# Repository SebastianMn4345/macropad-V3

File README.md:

# macropad-V3
 8-key with oled/slide pot -> no matrix

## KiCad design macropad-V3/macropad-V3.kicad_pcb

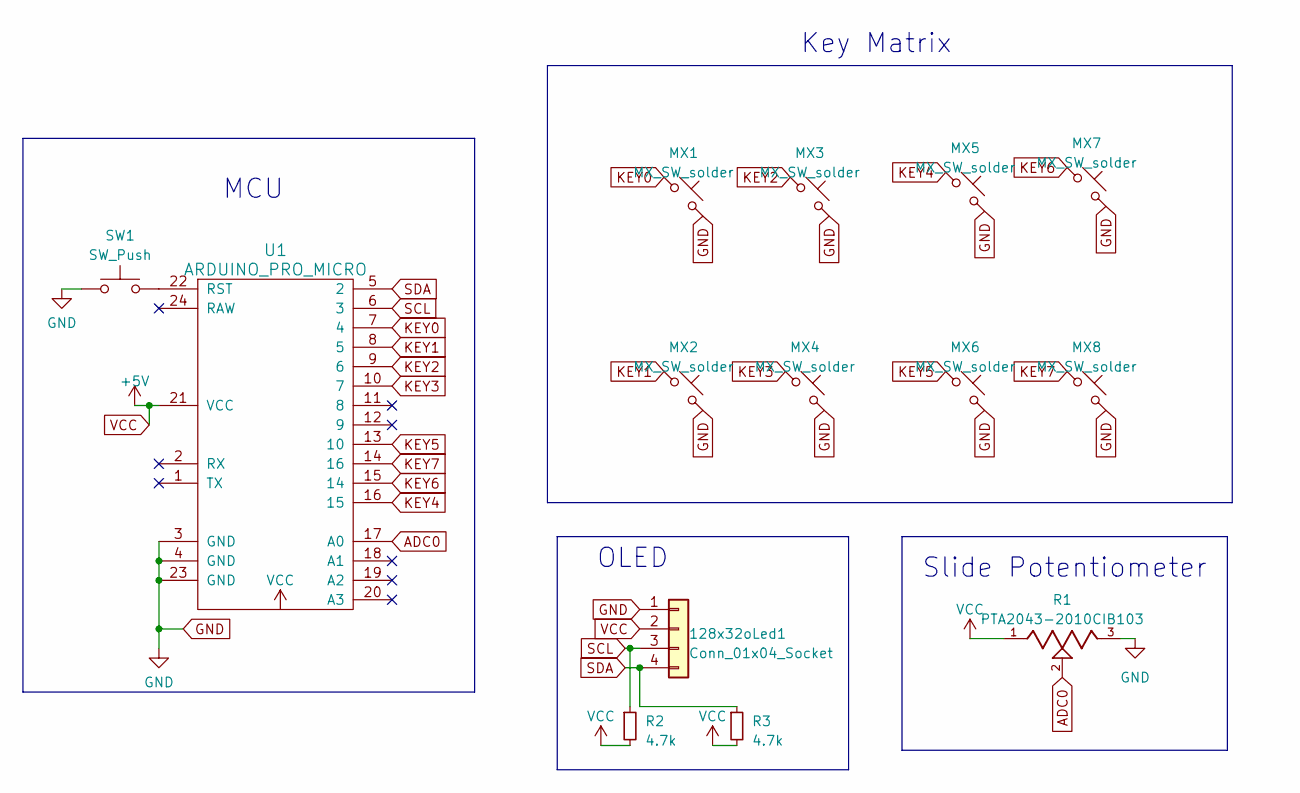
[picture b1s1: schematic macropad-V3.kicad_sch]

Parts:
128x32oLed1: Conn_01x04_Socket; SSD1306-0.91-OLED-4pin-128x32
MX1, MX2, MX3, MX4, MX5, MX6, MX7, MX8: MX_SW_solder; SW_Cherry_MX_1.00u_PCB
R1: PTA2043-2010CIB103; TRIM_PTA2043-2010CIB103; PARTREV 04/21
R2, R3: 4.7k; R_Axial_DIN0309_L9.0mm_D3.2mm_P12.70mm_Horizontal
SW1: SW_Push; SW_PUSH_6mm_H5mm
U1: ARDUINO_PRO_MICRO

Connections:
ADC0: R1.2, U1.17 (A0)
GND: 128x32oLed1.1, MX1.2, MX2.2, MX3.2, MX4.2, MX5.2, MX6.2, MX7.2, MX8.2, R1.3, SW1.1, U1.3 (GND), U1.4 (GND), U1.23 (GND)
KEY0: MX1.1, U1.7 (4)
KEY1: MX2.1, U1.8 (5)
KEY2: MX3.1, U1.9 (6)
KEY3: MX4.1, U1.10 (7)
KEY4: MX5.1, U1.16 (15)
KEY5: MX6.1, U1.13 (10)
KEY6: MX7.1, U1.15 (14)
KEY7: MX8.1, U1.14 (16)
unnamed: SW1.2, U1.22 (RST)
SCL: 128x32oLed1.3, R2.1, U1.6 (3)
SDA: 128x32oLed1.4, R3.1, U1.5 (2)
VCC: 128x32oLed1.2, R1.1, R2.2, R3.2, U1.21 (VCC)

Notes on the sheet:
Slide Potentiometer
OLED
Key Matrix
MCU

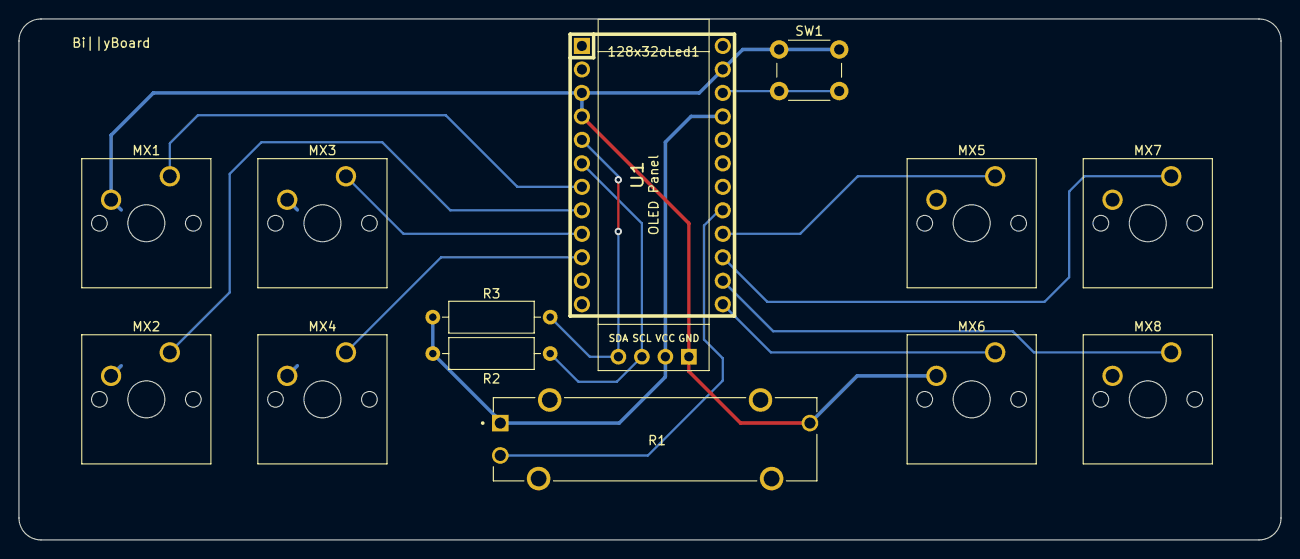
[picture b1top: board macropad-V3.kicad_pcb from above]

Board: 2 copper layers, 136.5 x 56.4 mm, 14 parts (0 on the bottom side), 14 nets.

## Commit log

2023-07-31 Removed Matrix/Direct to pin connections
    Good to go, DRC is all green
2023-07-31 Gerber Files added
2023-07-31 finalized schematic
2023-07-31 added pull up resistors/added ground plane/routed traces
2023-07-31 nothign changed
2023-08-03 updated routing
